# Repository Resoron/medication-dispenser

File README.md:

# Medicine Delivery System PCB (v1.0)

Custom controller board for an automatic medication dispenser — ENGE 1414, Group B10.

## Board overview
- **MCU:** ESP32-S3-WROOM-1-N8 (Wi-Fi/BLE, native USB for flashing)
- **Power:** USB-C (5 V) → NCP1117LP 3.3 V LDO; motors run directly from 5 V
- **Motors:** 4× 28BYJ-48 steppers driven by 2× ULN2803A (JST-XH 5-pin connectors J2–J5)
- **Display:** 16×2 LCD with PCF8574 I2C backpack, BSS138 3.3 V ↔ 5 V level shifter (JST-XH 4-pin, J6)
- **Inputs:** 3 external buttons (JST-XH 2-pin), on-board RESET and BOOT
- **Protection:** USBLC6-2SC6 ESD on USB D+/D−, 470 µF bulk cap on the motor rail

## GPIO map
| Function | GPIO |
|---|---|
| Motor 1 / 2 (ULN2803 #1) | IO4–7 / IO15–18 |
| Motor 3 / 4 (ULN2803 #2) | IO35–38 / IO39–42 |
| LCD I2C SDA / SCL | IO8 / IO9 |
| Buttons | IO1, IO2, IO14 |
| Status LED | IO21 |
| USB D− / D+ | IO19 / IO20 |
| Boot / Reset | IO0 / EN |
| Free (future homing sensors) | IO10–13, IO47, IO48 |

## Repository layout
```
hardware/     KiCad project (open Medication_System_Final.kicad_pro)
production/   Gerbers + drill files as ordered (gerbers.zip) and BOM.csv
```

## History
- `servo-c6` tag: earlier 2-servo design on an ESP32-C6
- `master`: final stepper design on the ESP32-S3 (the version that was ordered)

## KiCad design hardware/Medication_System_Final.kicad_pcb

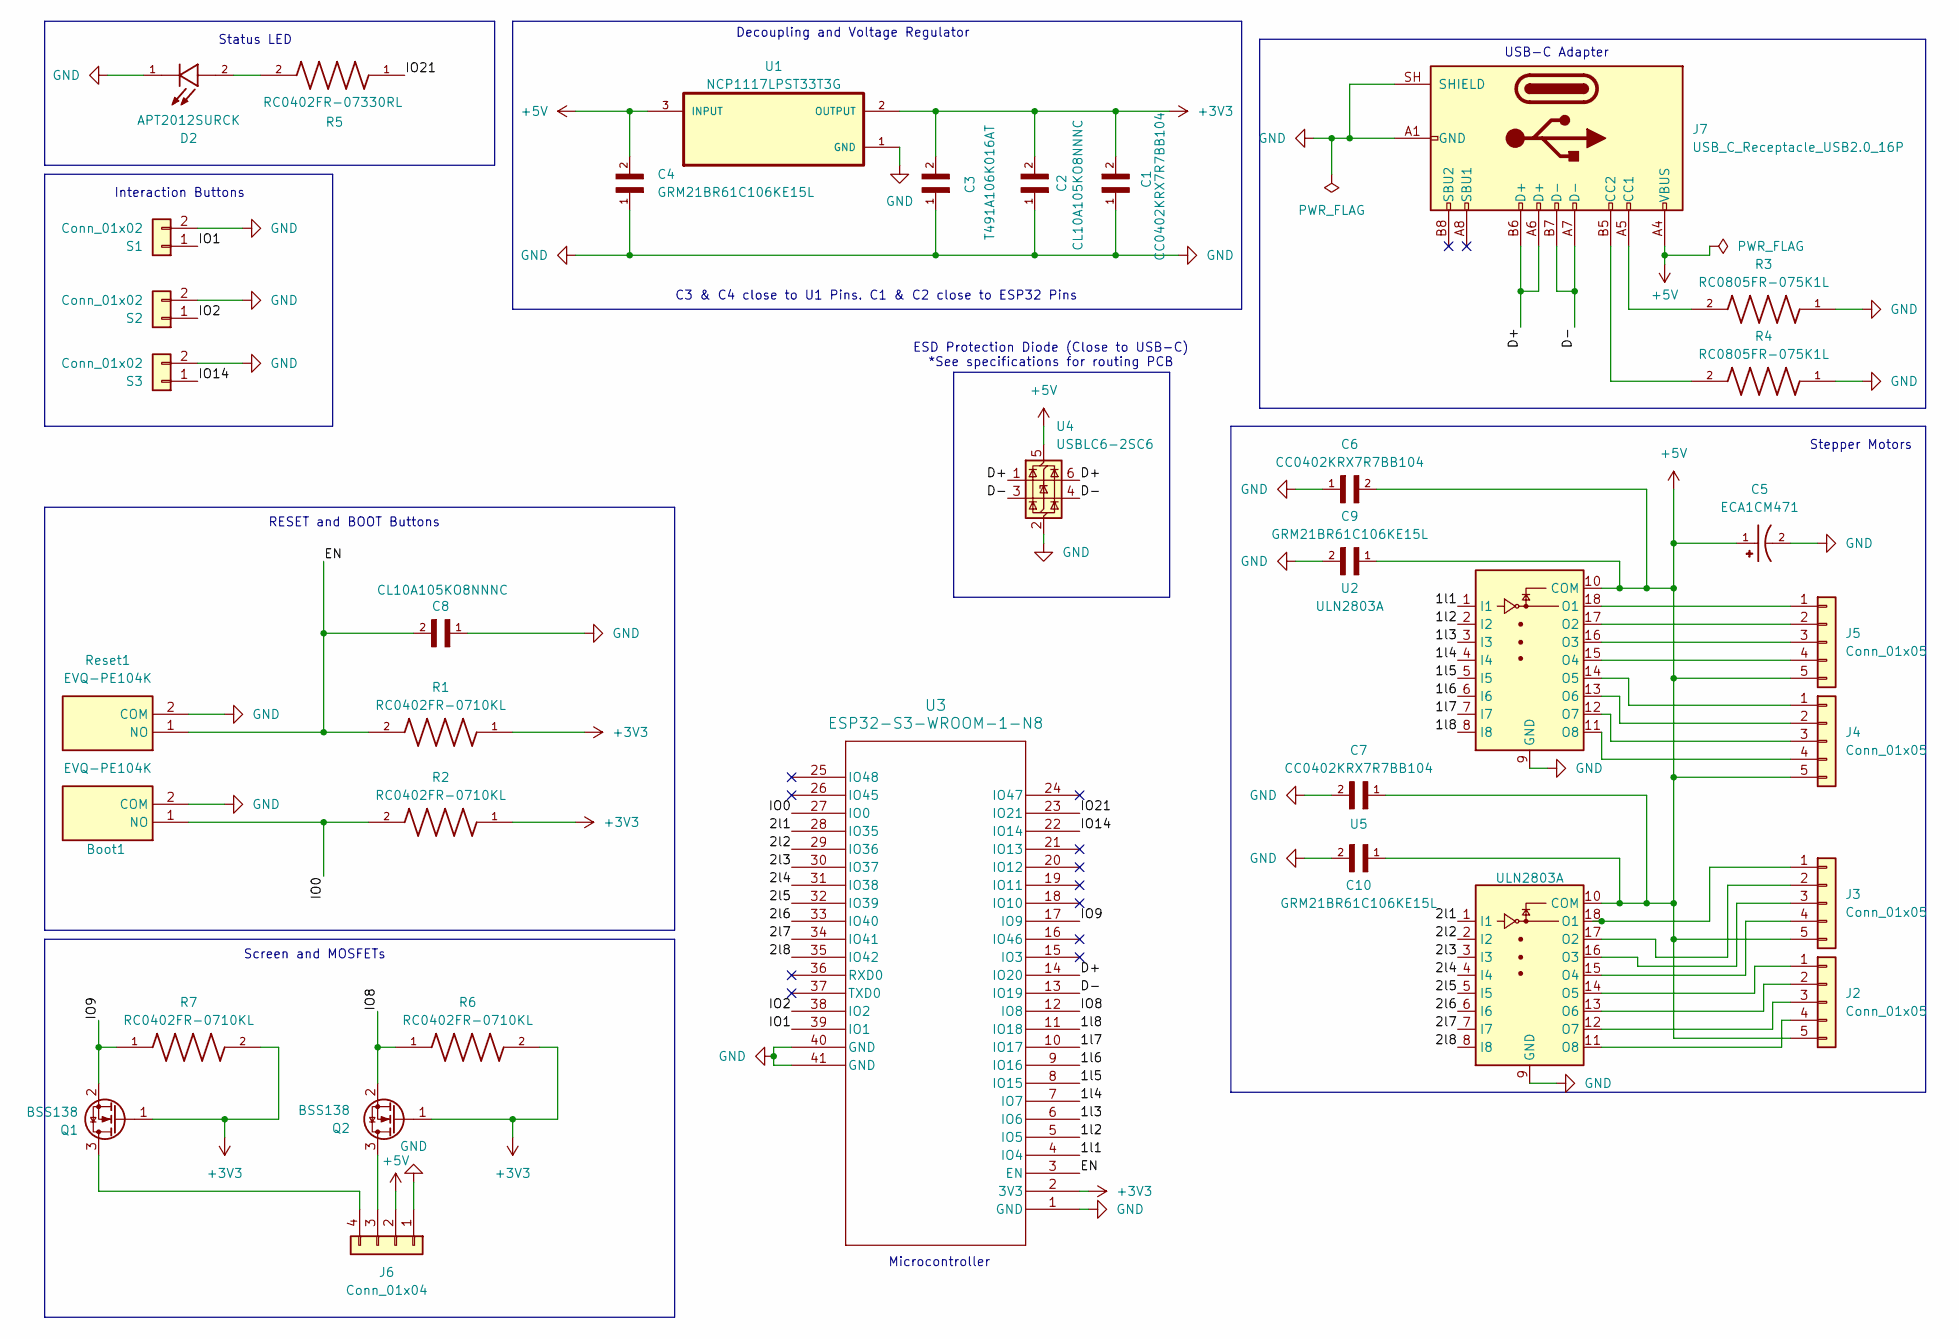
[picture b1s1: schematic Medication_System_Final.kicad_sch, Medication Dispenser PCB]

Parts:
Boot1: EVQ-PE104K; SW_SPST_EVQPE1; Mouser Part Number 667-EVQ-PE104K
C1, C6, C7: CC0402KRX7R7BB104; CAPC1005X55N
C2, C8: CL10A105KO8NNNC; CAPC1608X90N
C3: T491A106K016AT; RESC3216X125N
C4, C9, C10: GRM21BR61C106KE15L; CAPC2012X135N
C5: ECA1CM471; CP_Radial_D8.0mm_P3.50mm; PARTREV 20-DEC-19
D2: APT2012SURCK; LED_APT2012SURCK; PARTREV V.20B; DigiKey_Part_Number 754-1133-1-ND
J2, J3, J4, J5: Conn_01x05; JST_XH_B5B-XH-A_1x05_P2.50mm_Vertical
J6: Conn_01x04; JST_XH_B4B-XH-A_1x04_P2.50mm_Vertical
J7: USB_C_Receptacle_USB2.0_16P; USB_C_Receptacle_GCT_USB4105-xx-A_16P_TopMnt_Horizontal
Q1, Q2: BSS138; SOT-23
R1, R2, R6, R7: RC0402FR-0710KL; RESC1005X40N; PARTREV V.12; DigiKey_Part_Number 311-10.0KLRCT-ND
R3, R4: RC0805FR-075K1L; R_0805_2012Metric_Pad1.20x1.40mm_HandSolder
R5: RC0402FR-07330RL; RESC1005X40N; DigiKey_Part_Number 311-330LRCT-ND
Reset1: EVQ-PE104K; SW_SPST_EVQPE1; Mouser Part Number 667-EVQ-PE104K
S1, S2, S3: Conn_01x02; JST_XH_B2B-XH-A_1x02_P2.50mm_Vertical
U1: NCP1117LPST33T3G; SOT230P700X175-4N; DigiKey_Part_Number NCP1117LPST33T3GOSCT-ND
U2, U5: ULN2803A; SOIC-18W_7.5x11.6mm_P1.27mm
U3: ESP32-S3-WROOM-1-N8; ESP32-S3-WROOM-1
U4: USBLC6-2SC6; SOT-23-6

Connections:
+3V3: C1.2, C2.2, C3.2, Q1.1 (G), Q2.1 (G), R1.1, R2.1, R6.2, R7.2, U1.2 (OUTPUT), U1.4 (OUTPUT), U3.2 (3V3)
+5V: C4.2, C5.1, C6.2, C7.1, C9.1, C10.1, J2.5, J3.5, J4.5, J5.5, J6.2, J7.A4 (VBUS), J7.A9 (VBUS), J7.B4 (VBUS), J7.B9 (VBUS), U1.3 (INPUT), U2.10 (COM), U4.5 (VBUS), U5.10 (COM)
/1l1: U2.1 (I1), U3.4 (IO4)
/1l2: U2.2 (I2), U3.5 (IO5)
/1l3: U2.3 (I3), U3.6 (IO6)
/1l4: U2.4 (I4), U3.7 (IO7)
/1l5: U2.5 (I5), U3.8 (IO15)
/1l6: U2.6 (I6), U3.9 (IO16)
/1l7: U2.7 (I7), U3.10 (IO17)
/1l8: U2.8 (I8), U3.11 (IO18)
/2l1: U3.28 (IO35), U5.1 (I1)
/2l2: U3.29 (IO36), U5.2 (I2)
/2l3: U3.30 (IO37), U5.3 (I3)
/2l4: U3.31 (IO38), U5.4 (I4)
/2l5: U3.32 (IO39), U5.5 (I5)
/2l6: U3.33 (IO40), U5.6 (I6)
/2l7: U3.34 (IO41), U5.7 (I7)
/2l8: U3.35 (IO42), U5.8 (I8)
/D+: J7.A6 (D+), J7.B6 (D+), U3.14 (IO20), U4.1 (I/O1), U4.6 (I/O1)
/D-: J7.A7 (D-), J7.B7 (D-), U3.13 (IO19), U4.3 (I/O2), U4.4 (I/O2)
/EN: C8.2, R1.2, Reset1.1 (NO), U3.3 (EN)
/IO0: Boot1.1 (NO), R2.2, U3.27 (IO0)
/IO1: S1.1, U3.39 (IO1)
/IO2: S2.1, U3.38 (IO2)
/IO8: Q2.2 (S), R6.1, U3.12 (IO8)
/IO9: Q1.2 (S), R7.1, U3.17 (IO9)
/IO14: S3.1, U3.22 (IO14)
/IO21: R5.1, U3.23 (IO21)
GND: Boot1.2 (COM), C1.1, C2.1, C3.1, C4.1, C5.2, C6.1, C7.2, C8.1, C9.2, C10.2, D2.1, J6.1, J7.A1 (GND), J7.A12 (GND), J7.B1 (GND), J7.B12 (GND), J7.SH (SHIELD), R3.1, R4.1, Reset1.2 (COM), S1.2, S2.2, S3.2, U1.1 (GND), U2.9 (GND), U3.1 (GND), U3.40 (GND), U3.41 (GND), U4.2 (GND), U5.9 (GND)
unnamed: D2.2, R5.2
unnamed: J2.1, U5.14 (O5)
unnamed: J2.2, U5.13 (O6)
unnamed: J2.3, U5.12 (O7)
unnamed: J2.4, U5.11 (O8)
unnamed: J3.1, U5.18 (O1)
unnamed: J3.2, U5.17 (O2)
unnamed: J3.3, U5.16 (O3)
unnamed: J3.4, U5.15 (O4)
unnamed: J4.1, U2.14 (O5)
unnamed: J4.2, U2.13 (O6)
unnamed: J4.3, U2.12 (O7)
unnamed: J4.4, U2.11 (O8)
unnamed: J5.1, U2.18 (O1)
unnamed: J5.2, U2.17 (O2)
unnamed: J5.3, U2.16 (O3)
unnamed: J5.4, U2.15 (O4)
unnamed: J6.3, Q2.3 (D)
unnamed: J6.4, Q1.3 (D)
unnamed: J7.A5 (CC1), R3.2
unnamed: J7.B5 (CC2), R4.2

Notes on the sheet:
RESET and BOOT Buttons
Decoupling and Voltage Regulator
ESD Protection Diode (Close to USB-C) *See specifications for routing PCB
USB-C Adapter
Status LED
Interaction Buttons
Stepper Motors
Microcontroller
Screen and MOSFETs
C3 & C4 close to U1 Pins. C1 & C2 close to ESP32 Pins

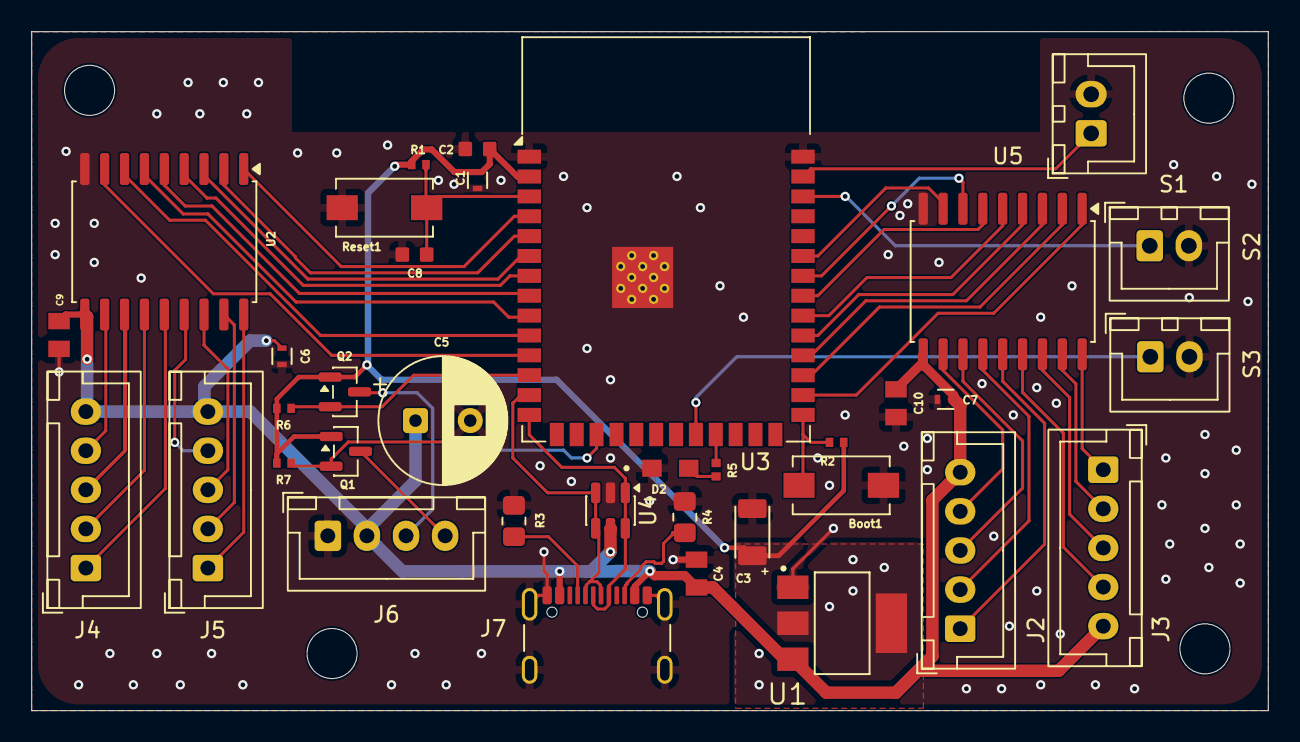
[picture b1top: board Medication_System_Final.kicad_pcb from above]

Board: 2 copper layers, 79.1 x 43.4 mm, 36 parts (0 on the bottom side), 50 nets.

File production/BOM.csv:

"Id";"Designator";"Footprint";"Quantity";"Designation";"Supplier and ref";
1;"Boot1, Reset1";"SW_SPST_EVQPE1";2;"EVQ-PE104K";;;
2;"C1, C6, C7";"CAPC1005X55N";3;"CC0402KRX7R7BB104";;;
3;"C2, C8";"CAPC1608X90N";2;"CL10A105KO8NNNC";;;
4;"C3";"RESC3216X125N";1;"T491A106K016AT";;;
5;"C4, C9, C10";"CAPC2012X135N";3;"GRM21BR61C106KE15L";;;
6;"C5";"CP_Radial_D8.0mm_P3.50mm";1;"ECA1CM471";;;
7;"D2";"LED_APT2012SURCK";1;"APT2012SURCK";;;
8;"J2, J3, J4, J5";"JST_XH_B5B-XH-A_1x05_P2.50mm_Vertical";4;"Conn_01x05";;;
9;"J6";"JST_XH_B4B-XH-A_1x04_P2.50mm_Vertical";1;"Conn_01x04";;;
10;"J7";"USB_C_Receptacle_GCT_USB4105-xx-A_16P_TopMnt_Horizontal";1;"USB_C_Receptacle_USB2.0_16P";;;
11;"Q1, Q2";"SOT-23";2;"BSS138";;;
12;"R1, R2, R6, R7";"RESC1005X40N";4;"RC0402FR-0710KL";;;
13;"R3, R4";"R_0805_2012Metric_Pad1.20x1.40mm_HandSolder";2;"RC0805FR-075K1L";;;
14;"R5";"RESC1005X40N";1;"RC0402FR-07330RL";;;
15;"S1, S2, S3";"JST_XH_B2B-XH-A_1x02_P2.50mm_Vertical";3;"Conn_01x02";;;
16;"U1";"SOT230P700X175-4N";1;"NCP1117LPST33T3G";;;
17;"U2, U5";"SOIC-18W_7.5x11.6mm_P1.27mm";2;"ULN2803A";;;
18;"U3";"ESP32-S3-WROOM-1";1;"ESP32-S3-WROOM-1-N8";;;
19;"U4";"SOT-23-6";1;"USBLC6-2SC6";;;

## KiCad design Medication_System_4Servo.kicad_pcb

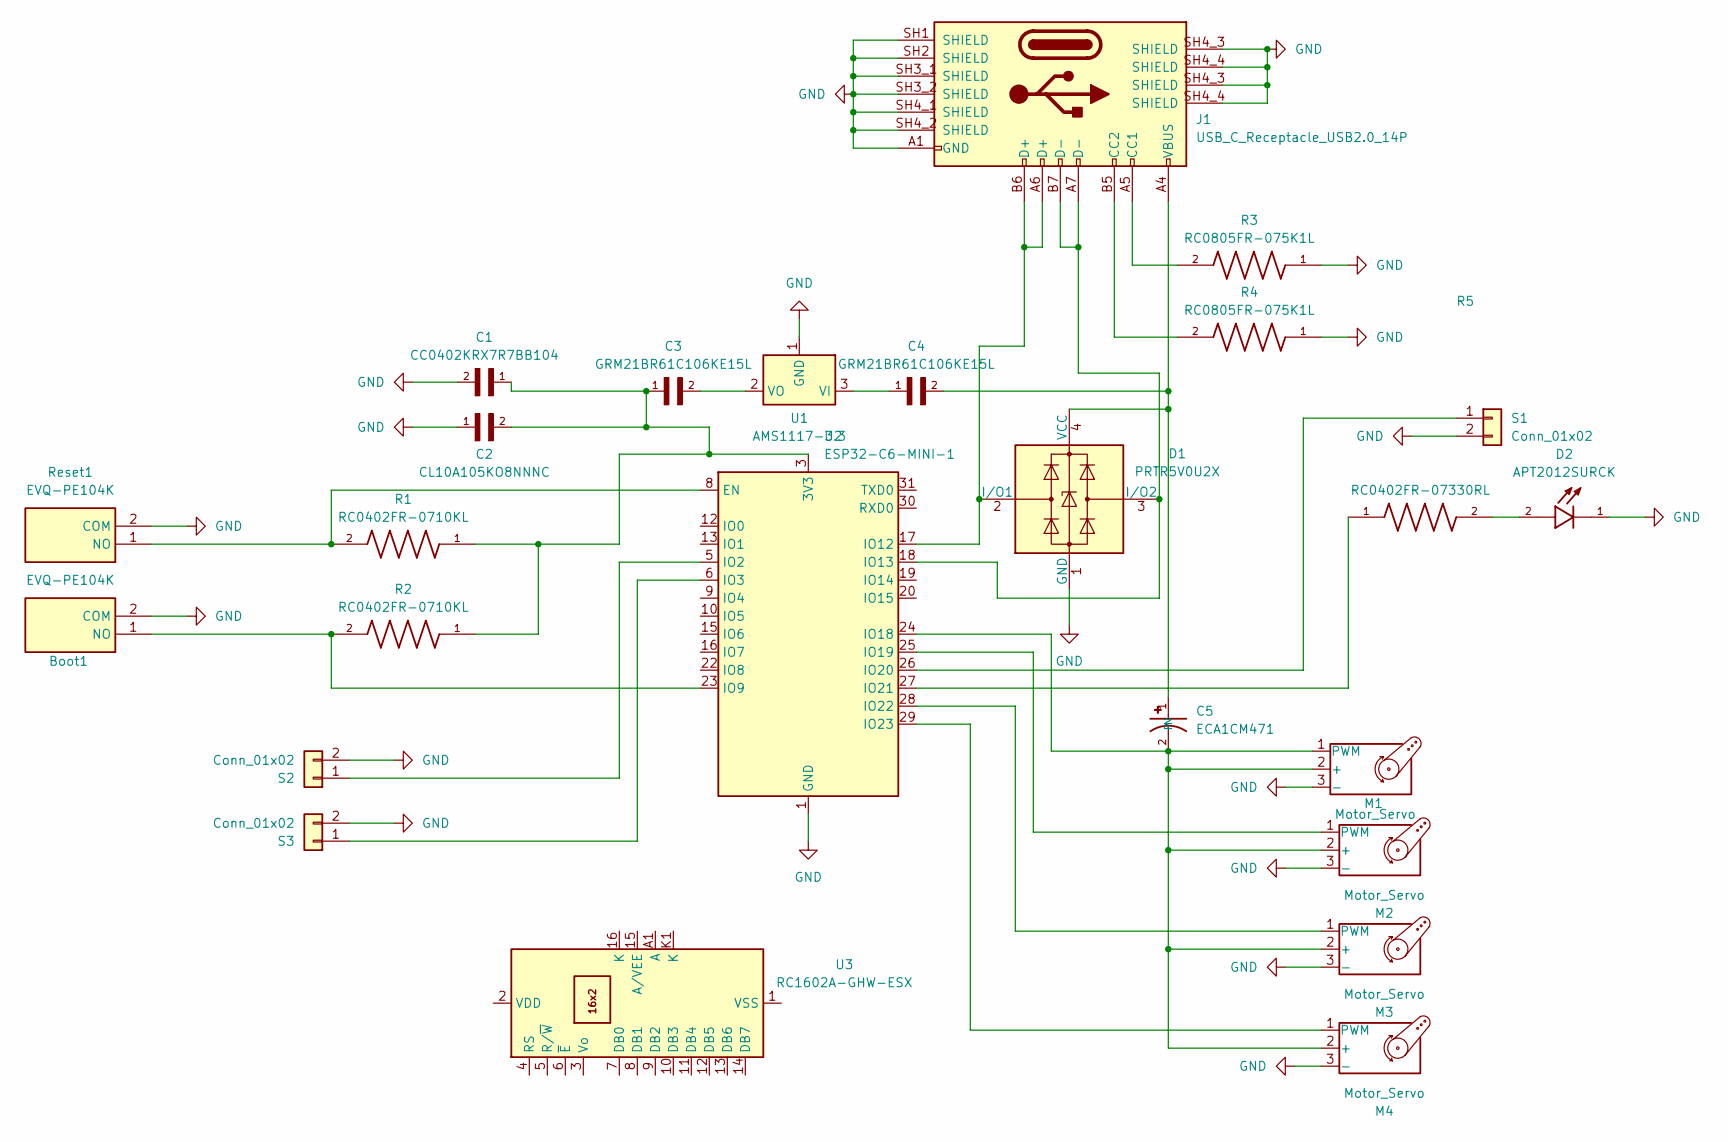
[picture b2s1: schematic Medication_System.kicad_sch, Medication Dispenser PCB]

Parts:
Boot1: EVQ-PE104K; SW_SPST_EVQPE1; Mouser Part Number 667-EVQ-PE104K
C1: CC0402KRX7R7BB104; CAPC1005X55N
C2: CL10A105KO8NNNC; CAPC1608X90N
C3, C4: GRM21BR61C106KE15L; CAPC2012X135N
C5: ECA1CM471; CP_Radial_D8.0mm_P3.50mm; PARTREV 20-DEC-19
D1: PRTR5V0U2X; SOT-143
D2: APT2012SURCK; LED_APT2012SURCK; PARTREV V.20B; DigiKey_Part_Number 754-1133-1-ND
J1: USB_C_Receptacle_USB2.0_14P; AMPHENOL_12401899E412A
M1, M2, M3, M4: Motor_Servo; PinHeader_1x03_P2.54mm_Vertical
R1, R2: RC0402FR-0710KL; RESC1005X40N; PARTREV V.12; DigiKey_Part_Number 311-10.0KLRCT-ND
R3, R4: RC0805FR-075K1L; R_0805_2012Metric
R5: RC0402FR-07330RL; RESC1005X40N; DigiKey_Part_Number 311-330LRCT-ND
Reset1: EVQ-PE104K; SW_SPST_EVQPE1; Mouser Part Number 667-EVQ-PE104K
S1, S2, S3: Conn_01x02; JWT_A3963_1x02_P3.96mm_Vertical
U1: AMS1117-3.3; SOT-223-3_TabPin2
U2: ESP32-C6-MINI-1
U3: RC1602A-GHW-ESX; RC1602A

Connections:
GND: Boot1.2 (COM), C1.2, C2.1, D1.1 (GND), D2.1, J1.A1 (GND), J1.A12 (GND), J1.B1 (GND), J1.B12 (GND), J1.SH1 (SHIELD), J1.SH2 (SHIELD), J1.SH3_1 (SHIELD), J1.SH3_2 (SHIELD), J1.SH4_1 (SHIELD), J1.SH4_2 (SHIELD), J1.SH4_3 (SHIELD), J1.SH4_4 (SHIELD), M1.3 (-), M2.3 (-), M3.3 (-), M4.3 (-), R3.1, R4.1, Reset1.2 (COM), S1.2, S2.2, S3.2, U1.1 (GND), U2.1 (GND), U2.2 (GND), U2.11 (GND), U2.14 (GND), U2.36 (GND), U2.37 (GND), U2.38 (GND), U2.39 (GND), U2.40 (GND), U2.41 (GND), U2.42 (GND), U2.43 (GND), U2.44 (GND), U2.45 (GND), U2.46 (GND), U2.47 (GND), U2.48 (GND), U2.49 (GND), U2.50 (GND), U2.51 (GND), U2.52 (GND), U2.53 (GND)
unnamed: Boot1.1 (NO), R2.2, U2.23 (IO9)
unnamed: C5.2 (N), M1.1 (PWM), M1.2 (+), M2.2 (+), M3.2 (+), M4.2 (+), U2.24 (IO18)
unnamed: C4.2, C5.1, D1.4 (VCC), J1.A4 (VBUS), J1.A9 (VBUS), J1.B4 (VBUS), J1.B9 (VBUS)
unnamed: D1.2 (I/O1), J1.A6 (D+), J1.B6 (D+), U2.17 (IO12)
unnamed: D1.3 (I/O2), J1.A7 (D-), J1.B7 (D-), U2.18 (IO13)
unnamed: D2.2, R5.2
unnamed: J1.A5 (CC1), R3.2
unnamed: J1.B5 (CC2), R4.2
unnamed: M2.1 (PWM), U2.25 (IO19)
unnamed: M3.1 (PWM), U2.28 (IO22)
unnamed: M4.1 (PWM), U2.29 (IO23)
unnamed: R1.2, Reset1.1 (NO), U2.8 (EN)
unnamed: S1.1, U2.26 (IO20)
unnamed: S2.1, U2.5 (IO2)
unnamed: S3.1, U2.6 (IO3)
unnamed: C4.1, U1.3 (VI)
unnamed: C3.2, U1.2 (VO)
unnamed: C1.1, C2.2, C3.1, R1.1, R2.1, U2.3 (3V3)
unnamed: R5.1, U2.27 (IO21)

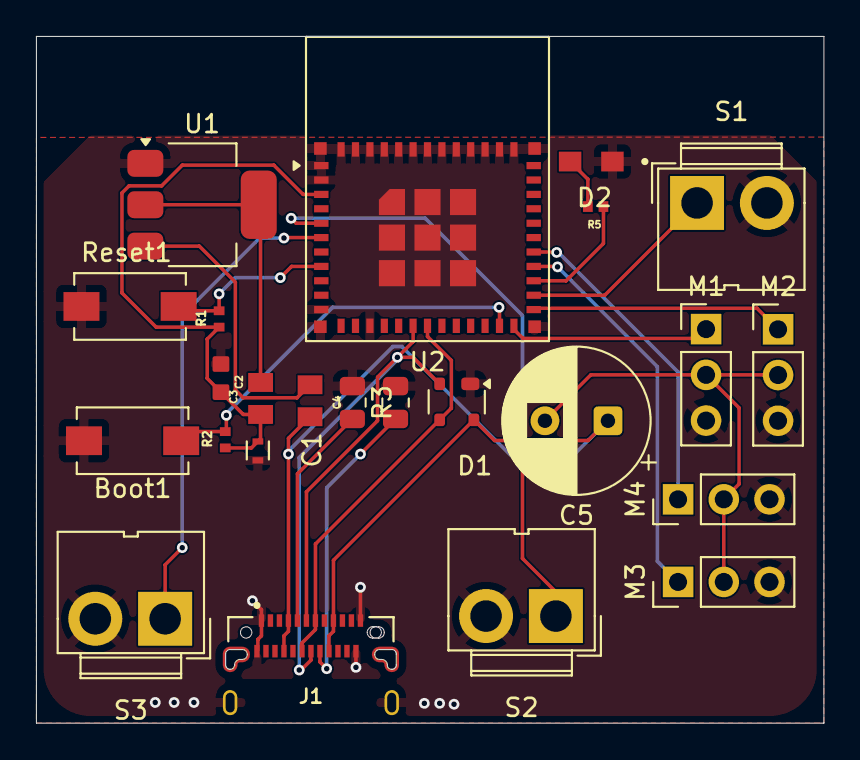
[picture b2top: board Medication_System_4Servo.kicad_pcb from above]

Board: 2 copper layers, 43.8 x 38.2 mm, 24 parts (0 on the bottom side), 20 nets.
